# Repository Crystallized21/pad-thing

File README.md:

# Crystallized's Pad Thing
This macro pad contains 12 keys, each containing RGB underglow and has a OLED Screen! This macropad uses QMK Firmware.

## What and Why?
I wanted to build my own macropad for at least for some uses cases. I couldn't think of any so I decided to emulating a mouse with this! Therefore I can control the mouse using "the keyboard" if you know what I mean! This could change in the near future when I can add modifiers to change between different key modes for different work flows!

Also I wanted to learn something new and get some hardware skills in, so this is a first step for me. Making my own PCB, trying out Fusion 360 for the first time and even coding my own firmware cause I like control! 😈

## BOM
- XIAO RP2040
- 12x 1N4148 Diodes
- 0.91 inch OLED Display
- 12x SK6812 RGB LEDs for each key.
- 12x Cherry MX Switches
- 4x M3x16 Bolt
- 4x M3 Heatset
- 12x Blank DSA Keycaps

## CAD Model

## Schematic

## PCB

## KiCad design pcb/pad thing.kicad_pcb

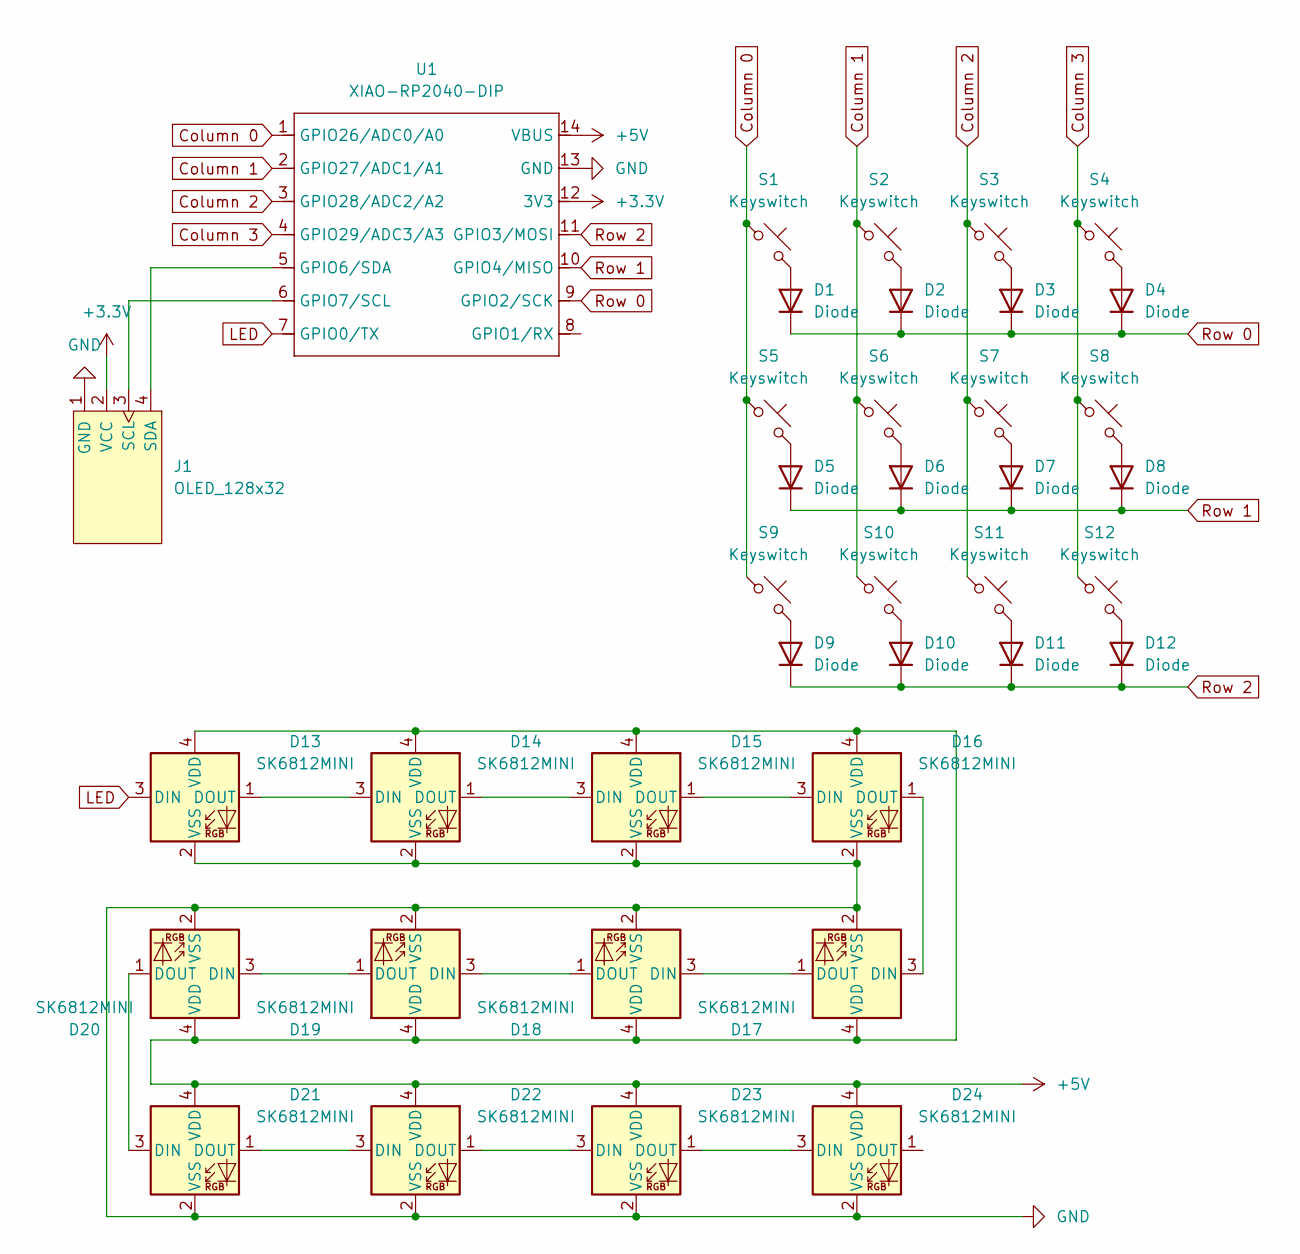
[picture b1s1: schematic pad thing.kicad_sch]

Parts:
D1, D2, D3, D4, D5, D6, D7, D8, D9, D10, D11, D12: Diode; Diode_DO-35
D13, D14, D15, D16, D17, D18, D19, D20, D21, D22, D23, D24: SK6812MINI; LED_SK6812MINI
J1: OLED_128x32
S1, S2, S3, S4, S5, S6, S7, S8, S9, S10, S11, S12: Keyswitch; MX_PCB_1.00u
U1: XIAO-RP2040-DIP

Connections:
+3.3V: J1.2 (VCC), U1.12 (3V3)
+5V: D13.4 (VDD), D14.4 (VDD), D15.4 (VDD), D16.4 (VDD), D17.4 (VDD), D18.4 (VDD), D19.4 (VDD), D20.4 (VDD), D21.4 (VDD), D22.4 (VDD), D23.4 (VDD), D24.4 (VDD), U1.14 (VBUS)
Column 0: S1.1, S5.1, S9.1, U1.1 (GPIO26/ADC0/A0)
Column 1: S2.1, S6.1, S10.1, U1.2 (GPIO27/ADC1/A1)
Column 2: S3.1, S7.1, S11.1, U1.3 (GPIO28/ADC2/A2)
Column 3: S4.1, S8.1, S12.1, U1.4 (GPIO29/ADC3/A3)
GND: D13.2 (VSS), D14.2 (VSS), D15.2 (VSS), D16.2 (VSS), D17.2 (VSS), D18.2 (VSS), D19.2 (VSS), D20.2 (VSS), D21.2 (VSS), D22.2 (VSS), D23.2 (VSS), D24.2 (VSS), J1.1 (GND), U1.13 (GND)
LED: D13.3 (DIN), U1.7 (GPIO0/TX)
unnamed: D1.2 (A), S1.2
unnamed: D2.2 (A), S2.2
unnamed: D3.2 (A), S3.2
unnamed: D4.2 (A), S4.2
unnamed: D5.2 (A), S5.2
unnamed: D6.2 (A), S6.2
unnamed: D7.2 (A), S7.2
unnamed: D8.2 (A), S8.2
unnamed: D9.2 (A), S9.2
unnamed: D10.2 (A), S10.2
unnamed: D11.2 (A), S11.2
unnamed: D12.2 (A), S12.2
unnamed: D13.1 (DOUT), D14.3 (DIN)
unnamed: D14.1 (DOUT), D15.3 (DIN)
unnamed: D15.1 (DOUT), D16.3 (DIN)
unnamed: D16.1 (DOUT), D17.3 (DIN)
unnamed: D17.1 (DOUT), D18.3 (DIN)
unnamed: D18.1 (DOUT), D19.3 (DIN)
unnamed: D19.1 (DOUT), D20.3 (DIN)
unnamed: D20.1 (DOUT), D21.3 (DIN)
unnamed: D21.1 (DOUT), D22.3 (DIN)
unnamed: D22.1 (DOUT), D23.3 (DIN)
unnamed: D23.1 (DOUT), D24.3 (DIN)
unnamed: J1.3 (SCL), U1.6 (GPIO7/SCL)
unnamed: J1.4 (SDA), U1.5 (GPIO6/SDA)
Row 0: D1.1 (K), D2.1 (K), D3.1 (K), D4.1 (K), U1.9 (GPIO2/SCK)
Row 1: D5.1 (K), D6.1 (K), D7.1 (K), D8.1 (K), U1.10 (GPIO4/MISO)
Row 2: D9.1 (K), D10.1 (K), D11.1 (K), D12.1 (K), U1.11 (GPIO3/MOSI)

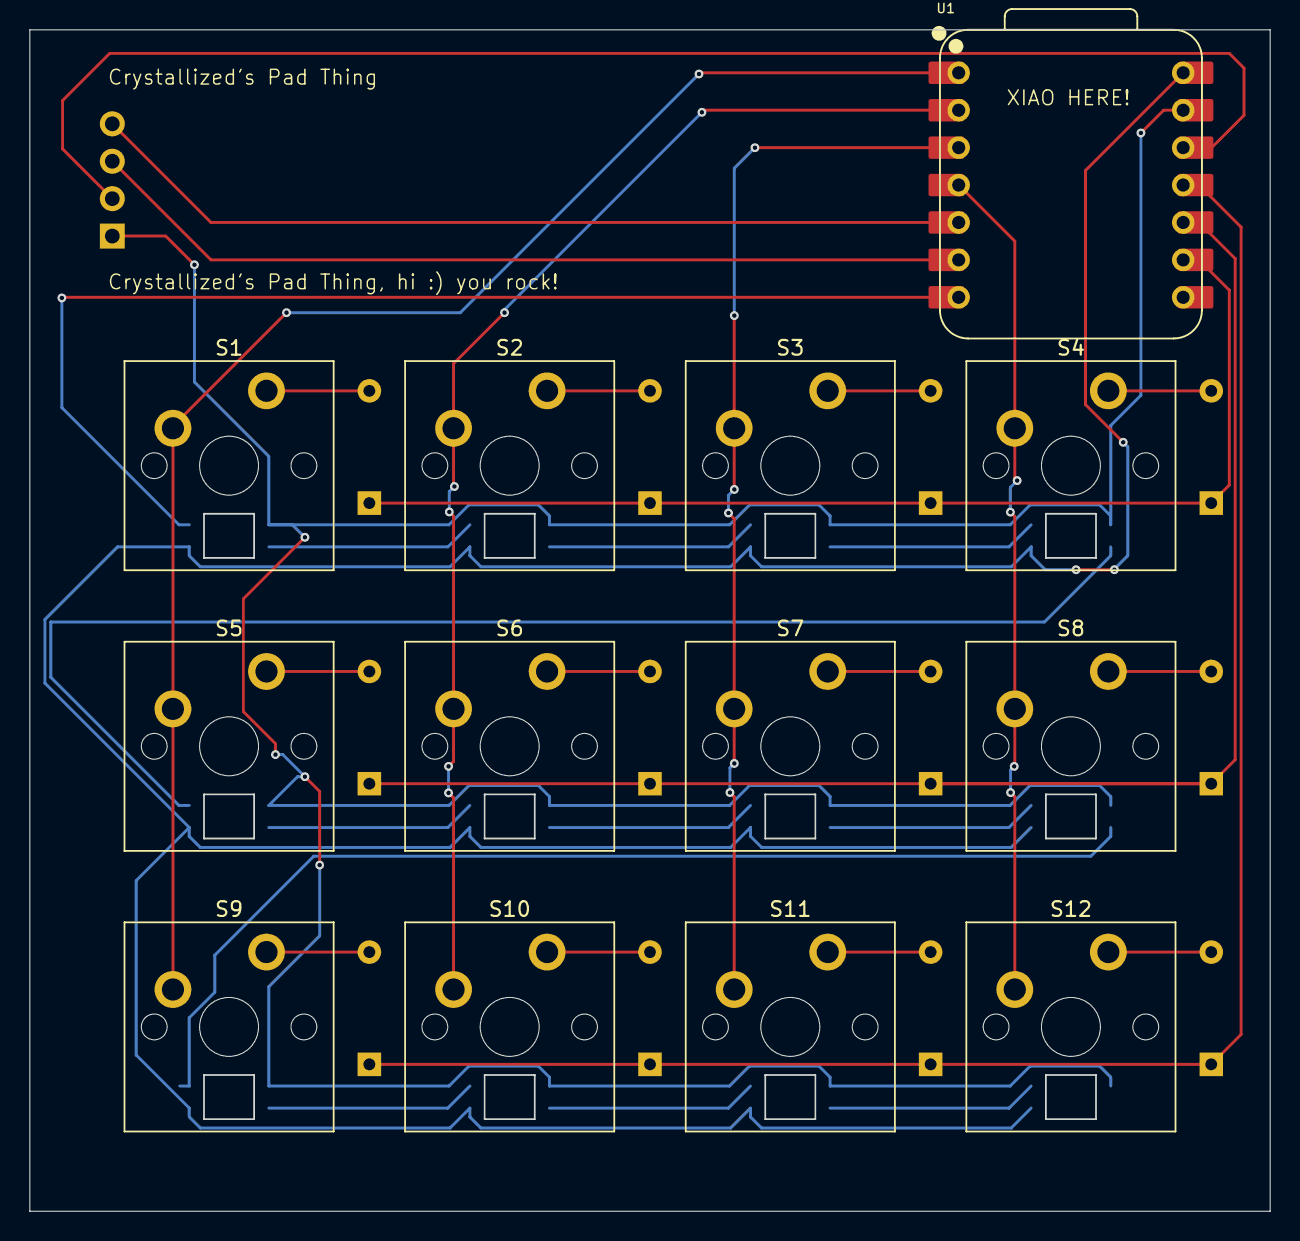
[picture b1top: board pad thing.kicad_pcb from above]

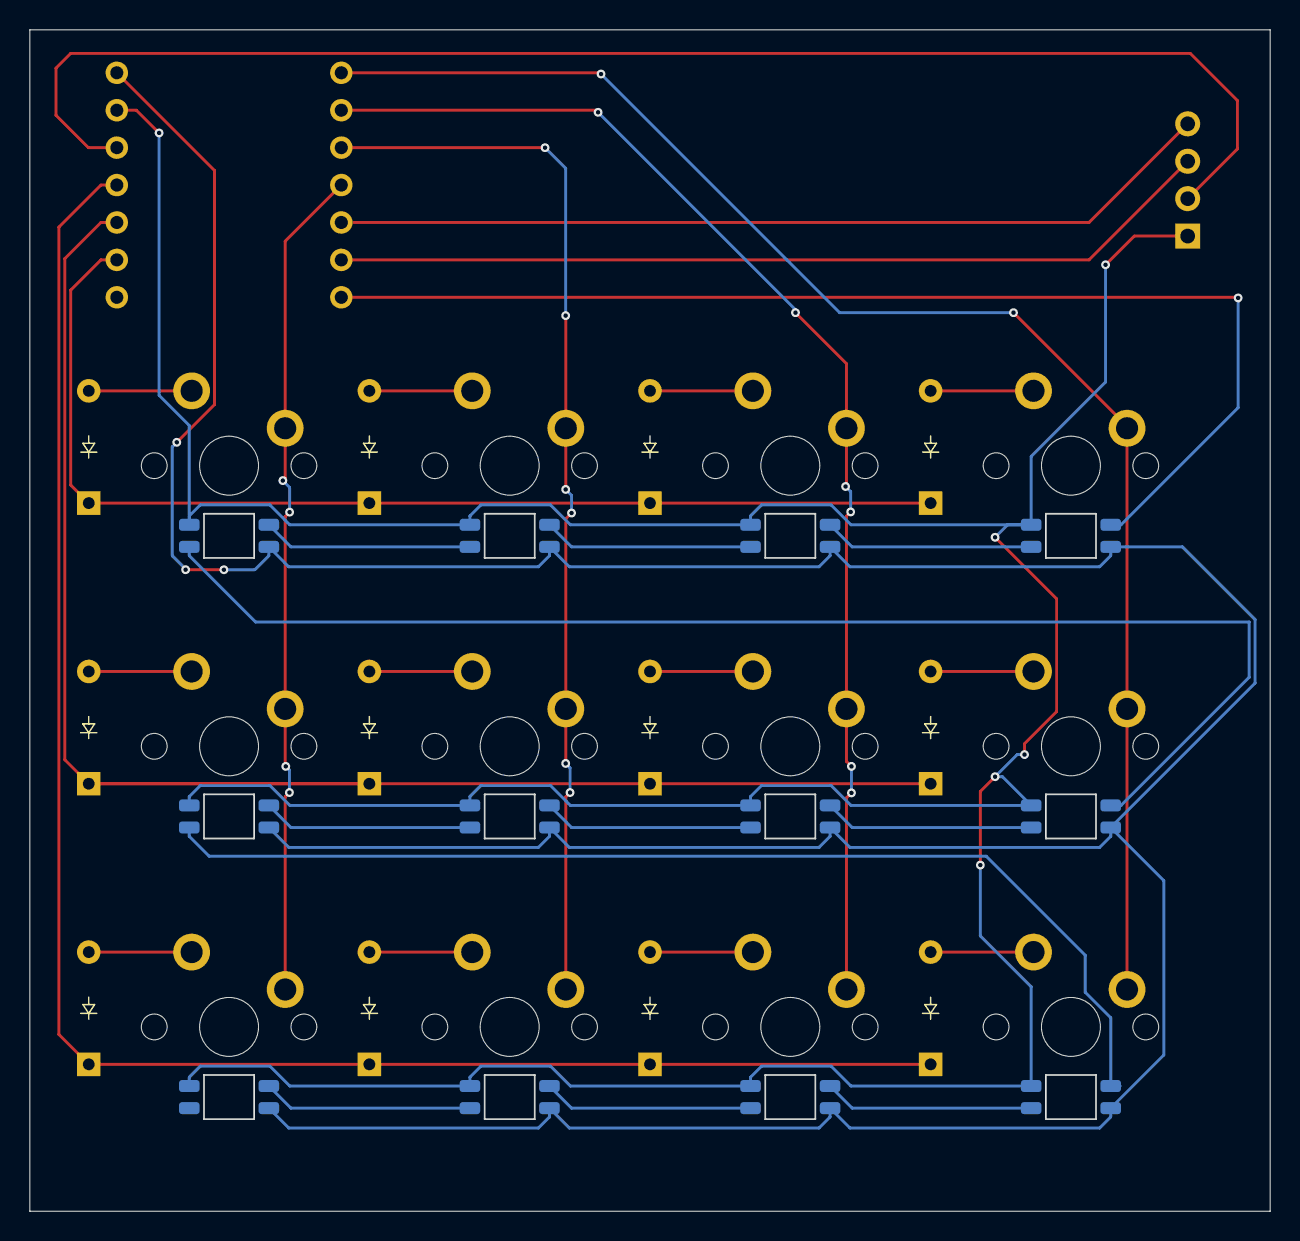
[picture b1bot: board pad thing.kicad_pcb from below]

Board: 2 copper layers, 84.2 x 80.2 mm, 38 parts (24 on the bottom side), 36 nets.

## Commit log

2025-07-02 add project files
2025-07-03 include diodes
